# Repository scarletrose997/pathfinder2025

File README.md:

##Memory Madness
##A memory game where the LED's lights up a random pattern that you must repeat. Each round adds an extra light to the sequence. If you fail, the game resets. How far can you make it?

##Schematic

##PCB Front

##PCB Back

##Tech
- Designed in KiCad
- Programmed using Arduino/C++

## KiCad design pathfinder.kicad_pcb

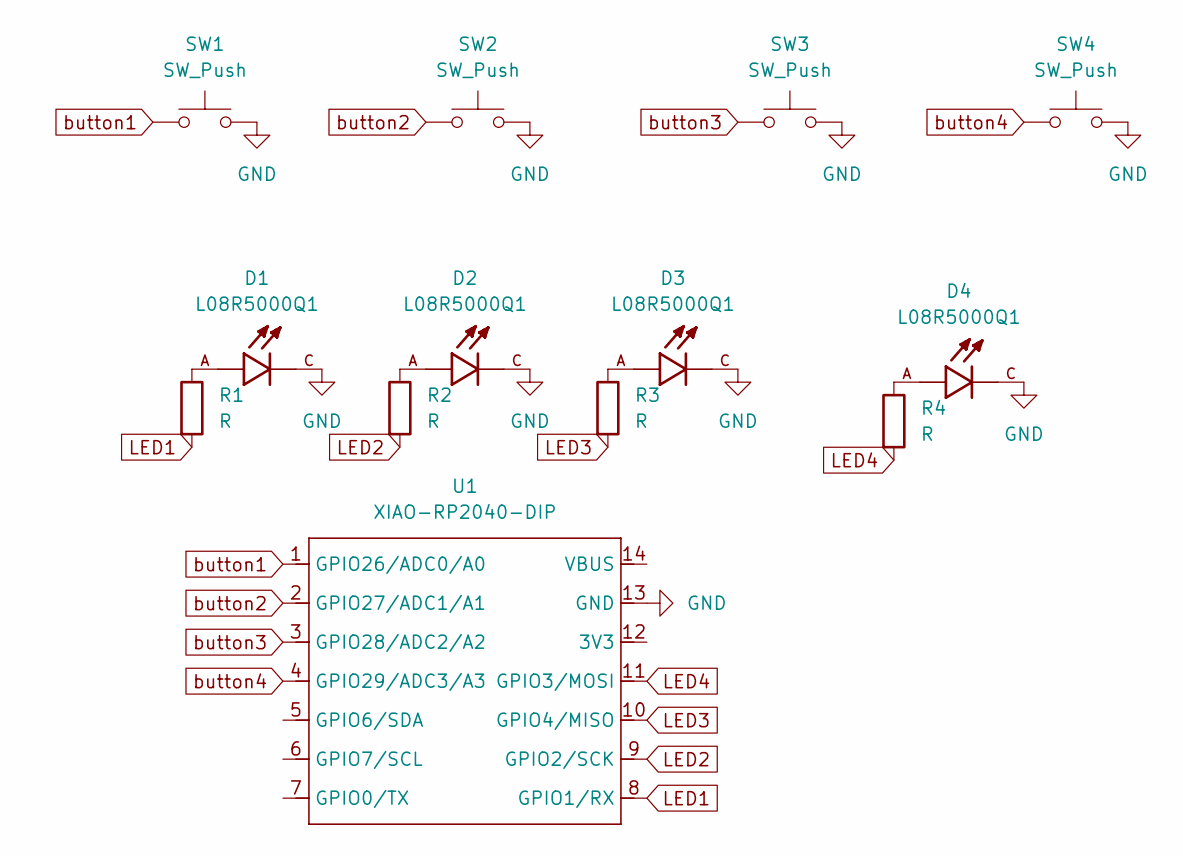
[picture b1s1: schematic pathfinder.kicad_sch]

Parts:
D1, D2, D3, D4: L08R5000Q1; LEDRD254W57D500H1070; PARTREV NA
R1, R2, R3, R4: R; R_Axial_DIN0204_L3.6mm_D1.6mm_P5.08mm_Horizontal
SW1, SW2, SW3, SW4: SW_Push; SW_Cherry_MX_1.00u_PCB
U1: XIAO-RP2040-DIP

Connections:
GND: D1.C, D2.C, D3.C, D4.C, SW1.2, SW2.2, SW3.2, SW4.2, U1.13 (GND)
LED1: R1.2, U1.8 (GPIO1/RX)
LED2: R2.2, U1.9 (GPIO2/SCK)
LED3: R3.2, U1.10 (GPIO4/MISO)
LED4: R4.2, U1.11 (GPIO3/MOSI)
unnamed: D1.A, R1.1
unnamed: D2.A, R2.1
unnamed: D3.A, R3.1
unnamed: D4.A, R4.1
button1: SW1.1, U1.1 (GPIO26/ADC0/A0)
button2: SW2.1, U1.2 (GPIO27/ADC1/A1)
button3: SW3.1, U1.3 (GPIO28/ADC2/A2)
button4: SW4.1, U1.4 (GPIO29/ADC3/A3)

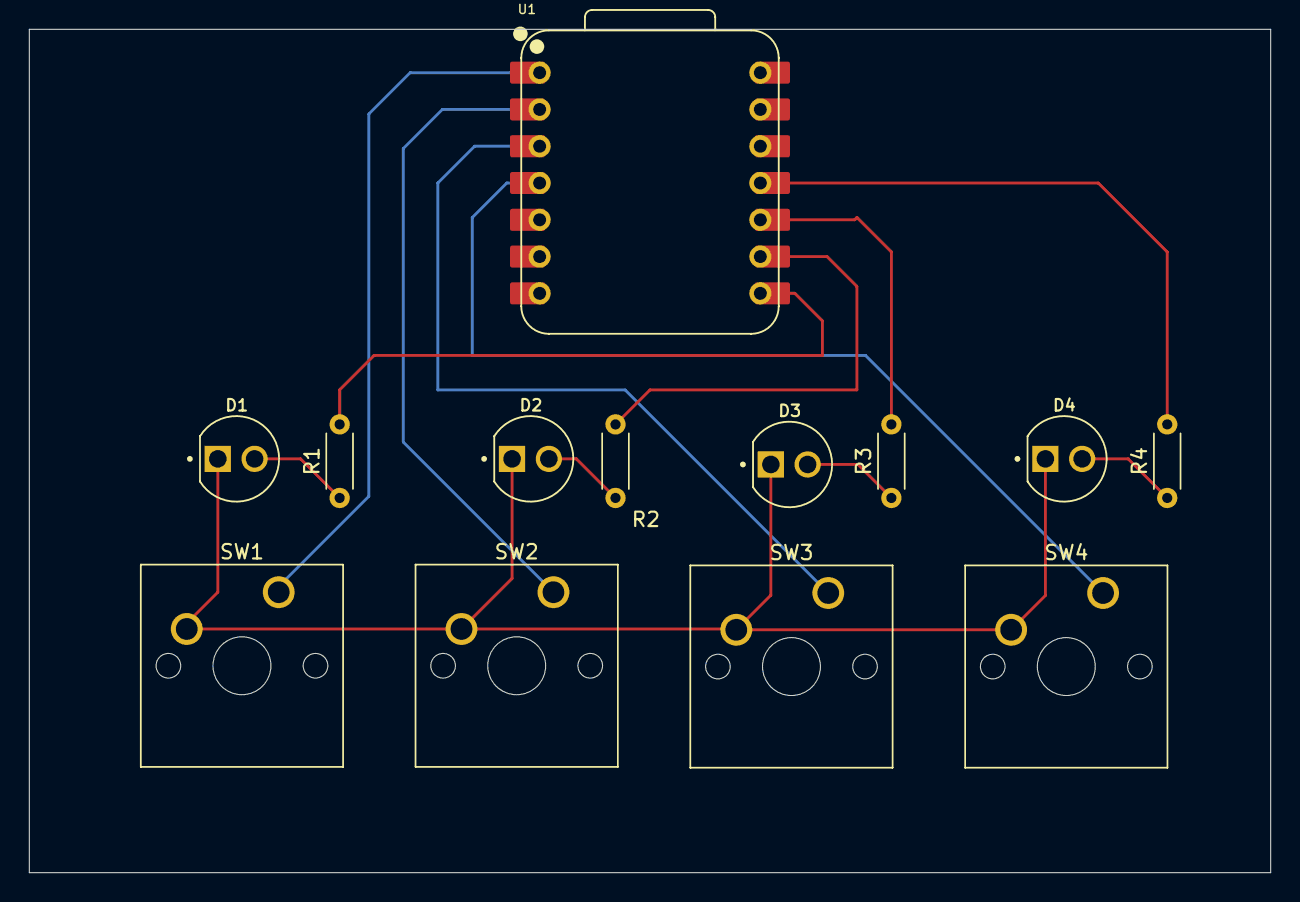
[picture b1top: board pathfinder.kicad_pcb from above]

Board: 2 copper layers, 85.7 x 58.2 mm, 13 parts (0 on the bottom side), 13 nets.

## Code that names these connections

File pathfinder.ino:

int KEY1 = D0;
int KEY2 = D1;
int KEY3 = D2;
int KEY4 = D3;

int LED1 = D11;
int LED2 = D10;
int LED3 = D9;
int LED4 = D8;

int KEYS[4];
int LEDS[4];

const int MAX_LENGTH = 50;
int sequence[MAX_LENGTH];
int numOfRounds=1;

void setup(){
    KEYS[0] = KEY1;
    KEYS[1] = KEY2;
    KEYS[2] = KEY3;
    KEYS[3] = KEY4;
    LEDS[0] = LED1;
    LEDS[1] = LED2;
    LEDS[2] = LED3;
    LEDS[3] = LED4;

    for(int i=0; i<4; i++){
        pinMode(KEYS[i], INPUT_PULLUP);
        pinMode(LEDS[i], OUTPUT);
    }

    randomSeed(analogRead(0));
    newSequence();
    long startTime = millis();

}

void loop(){
    playPattern();

    if (!playerTurn()){
        allLightOn(3,200 );
        numOfRounds=1;
        newSequence();

    }else{
        delay(250);
        numOfRounds++;
        newSequence();
    }
    delay(1000);
}

void playPattern() {
    for (int i = 0; i < numOfRounds; i++) {
        int ledIndex = sequence[i];
        digitalWrite(LEDS[ledIndex], HIGH);
        delay(400);
        digitalWrite(LEDS[ledIndex], LOW);
        delay(200);
    }
}

bool playerTurn() {
    for (int i = 0; i < numOfRounds; i++) {
        int input = pendingKeypress();
        if (input != sequence[i]) {
        return false;
        }
    }
  return true;
}

int pendingKeypress() {
    while (true) {
        for (int i = 0; i < 4; i++) {
        if (digitalRead(KEYS[i]) == LOW) {
            digitalWrite(LEDS[i], HIGH);
            delay(200);
            digitalWrite(LEDS[i], LOW);
            waitUnpress(i);
            return i;
        }
        }
    }
}

void waitUnpress(int i) {
    while (digitalRead(KEYS[i]) == LOW) {
        delay(10);
    }
}

void allLightOn(int times, int delayTime) {
    for (int t = 0; t < times; t++) {
        for (int i = 0; i < 4; i++) {
        digitalWrite(LEDS[i], HIGH);
        }
        delay(delayTime);
        for (int i = 0; i < 4; i++) {
        digitalWrite(LEDS[i], LOW);
        }
        delay(delayTime);
    }
}

void newSequence() {
    for (int i = 0; i < numOfRounds; i++) {
        sequence[i] = random(0, 4);
    }
}
